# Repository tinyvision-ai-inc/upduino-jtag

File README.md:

# JTAG translator using UPduino

We have an FTDI FT232 on the UPduino which is what is typically used in various JTAG debuggers. The ICE40 FPGA enables level translation as well as a UART interface which is typically used for debugging.

## Connections:
1. Cut the Bank 2 VIO sel jumper and short it to VIO. This allows the FPGA bank to be powered from the VIO pin which can be set to the VREF signal from the JTAG port.
2. Make the following connections:

  | Signal | Pin     |
  |--------|---------|
  | TCK    | gpio_2  |
  | TDI    | gpio_47 |
  | TDO    | gpio_46 |
  | TMS    | gpio_45 |
  | RXD    | gpio_48 |
  | TXD    | gpio_3  |
  | RSTn   | gpio_4  |
  | Ground | Ground  |
  | VIO    | VREF    |

In case the target is a 1.8V system, a cheap way to avoid the VREF line is to use a resistive voltage divider to source the VIO pin. This isnt optimal but should work since the power draw from the IO is pretty small. Use 2 470 ohm resistors to divide the 3.3V which will result in 1.65V as the logic level, not ideal but close.

Mapping to the FPGA pins:

| Pin | Signal | Pin | Signal |
|-----|--------|-----|--------|
| 1   | Vref   | 2   | TMS (45) |
| 3   | GND    | 4   | TCK (2) |
| 5   | GND    | 6   | TDO (46) |
| 7   | TXD    | 8   | TDI (47) |
| 9   | RXD    | 10  | RSTn (4) |

## Selection between UART and JTAG

There appears to be no way to select between when the FTDI wants to use its IO as JTAG vs. UART. Rather than being clever about it, we can simply use a manual jumper for this.

`gpio_42` is setup as a `JTAG_SELECT` pin and a 10K pullups is added to this pin in the FPGA constraints file. `gpio_38` is set low in the FPGA.

- UART mode: Add jumper between `gpio_38` and `gpio_42`. The green LED on the UPduino goes `OFF` indicate this.
- JTAG MODE: Remove jumper between `gpio_38` and `gpio_42`. The green LED on the UPduino comes `ON` to indicate this.

## Pogo probe adapter

While its nice to have a standard 10 pin JTAG connector, this takes up significant board space. By moving these pins to a series of pads, we can save space. Alterntively, these can be moved as castellations on the edge of the board to save even more space.

A pogo probe connector such as [854-22-006-20-041101 from Millmax](https://www.digikey.com/en/products/detail/mill-max-manufacturing-corp/854-22-006-20-041101/24634760?s=N4IgTCBcDaIBwFYAsBaMYUAZMDY2ayQEYjMiQBdAXyA) makes a robust way to connect to the debug pads.

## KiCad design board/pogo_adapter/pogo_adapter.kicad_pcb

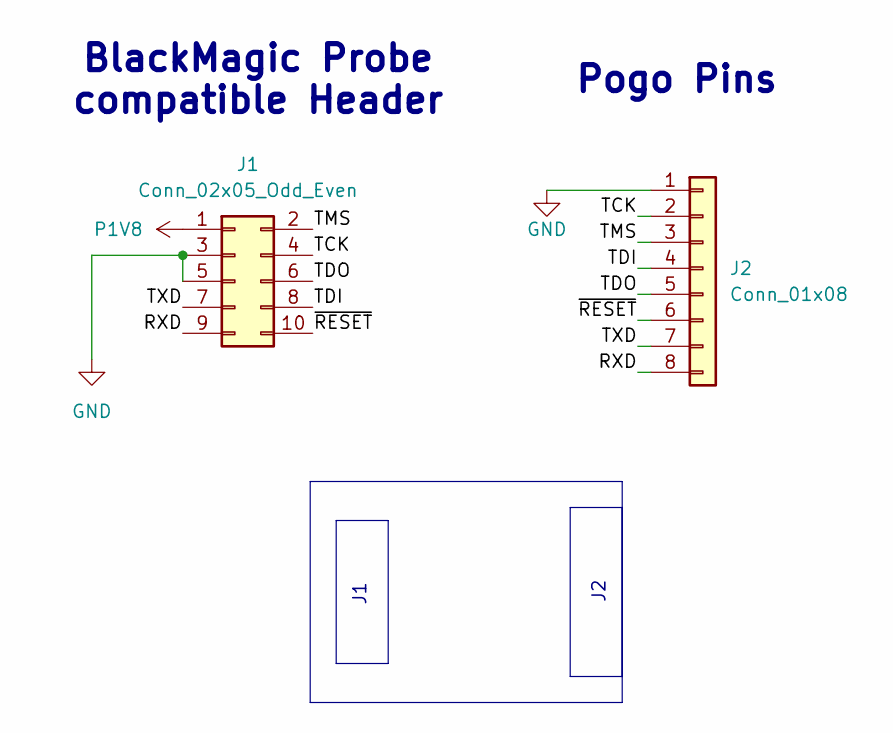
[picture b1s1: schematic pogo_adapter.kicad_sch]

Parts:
J1: Conn_02x05_Odd_Even; PinHeader_2x05_P1.27mm_Vertical_SMD
J2: Conn_01x08; PinHeader_1x08_P1.27mm_Horizontal

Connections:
/RXD: J1.9, J2.8
/TCK: J1.4, J2.2
/TDI: J1.8, J2.4
/TDO: J1.6, J2.5
/TMS: J1.2, J2.3
/TXD: J1.7, J2.7
/~RESET: J1.10, J2.6
GND: J1.3, J1.5, J2.1
P1V8: J1.1

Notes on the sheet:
Pogo Pins
BlackMagic Probe compatible Header

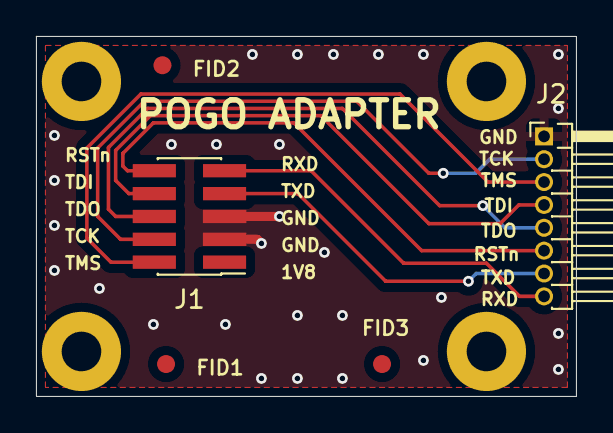
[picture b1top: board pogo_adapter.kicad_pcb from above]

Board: 2 copper layers, 30.0 x 20.0 mm, 9 parts (0 on the bottom side), 8 nets.

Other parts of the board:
FID1, FID2, FID3: Fiducial_1mm_Mask2mm
M1, M2, M3, M4: MountingHole_2.2mm_M2_Pad

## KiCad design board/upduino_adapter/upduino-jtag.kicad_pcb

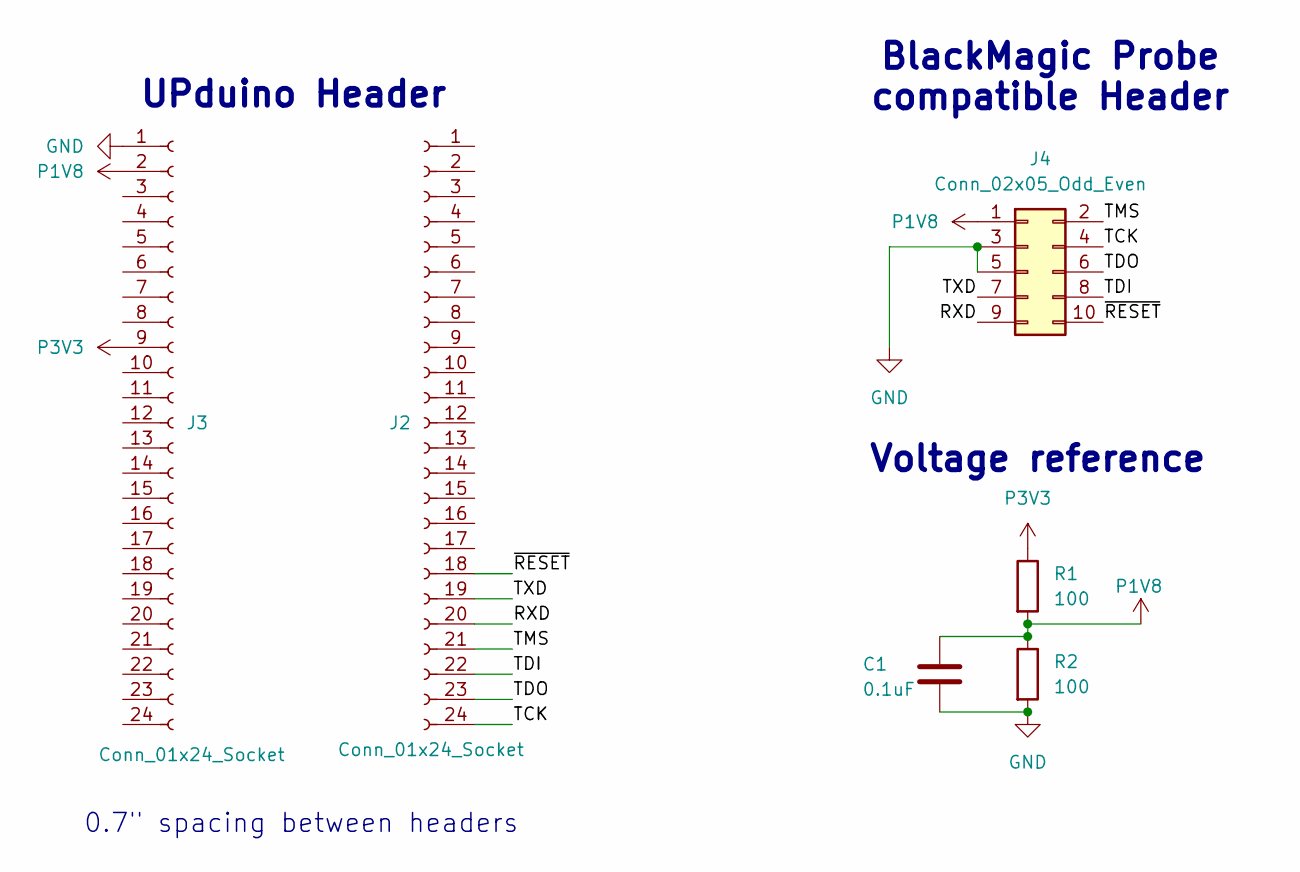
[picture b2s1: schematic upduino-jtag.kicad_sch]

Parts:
C1: 0.1uF; C_0603_1608Metric_Pad1.08x0.95mm_HandSolder
J2, J3: Conn_01x24_Socket; PinHeader_1x24_P2.54mm_Vertical
J4: Conn_02x05_Odd_Even; PinHeader_2x05_P1.27mm_Vertical_SMD
R1, R2: 100; R_0603_1608Metric_Pad0.98x0.95mm_HandSolder

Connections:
/RXD: J2.20, J4.9
/TCK: J2.24, J4.4
/TDI: J2.22, J4.8
/TDO: J2.23, J4.6
/TMS: J2.21, J4.2
/TXD: J2.19, J4.7
/~RESET: J2.18, J4.10
GND: C1.2, J3.1, J4.3, J4.5, R2.2
P1V8: C1.1, J3.2, J4.1, R1.2, R2.1
P3V3: J3.9, R1.1

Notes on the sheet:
BlackMagic Probe compatible Header
0.7" spacing between headers
UPduino Header
Voltage reference

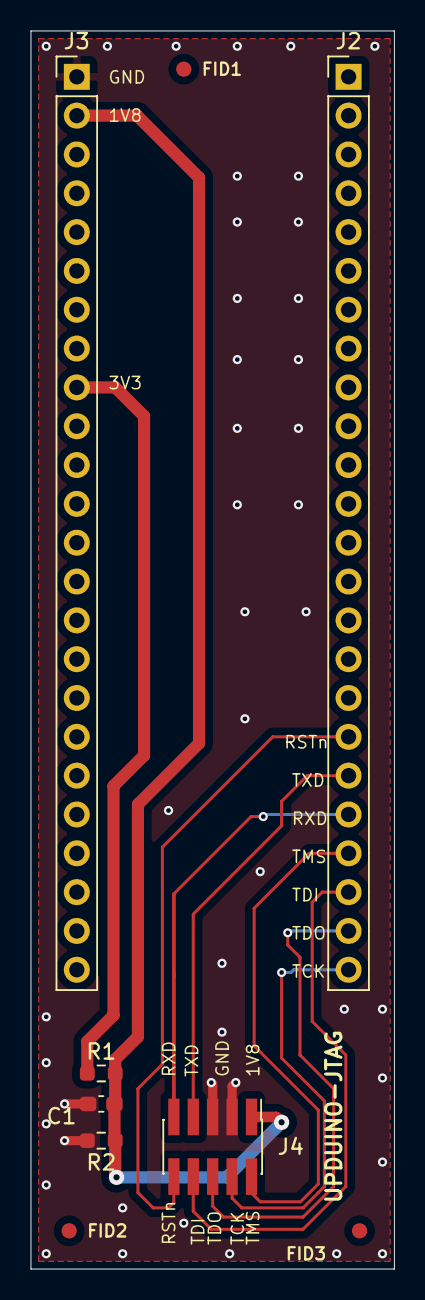
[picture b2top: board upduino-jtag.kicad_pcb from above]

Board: 2 copper layers, 23.8 x 81.0 mm, 9 parts (0 on the bottom side), 10 nets.

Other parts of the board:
FID1, FID2, FID3: Fiducial_1mm_Mask2mm

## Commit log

2025-01-20 Added RTL files
2025-01-20 Added schematic
2025-01-20 Added pogo adapter
2025-01-20 Added details of pogo probe to readme
2025-01-22 updated design files and output files
2025-01-22 Added image
2025-08-27 Removed debug and changed GPIO_4 to be high to set the JTAG_EN high
2025-10-26 Added UART functionality and tested to wrok
2025-12-18 Added docs for UART vs JTAG selection
2025-12-18 Fixed copy-paste error on text in drawing annotation
